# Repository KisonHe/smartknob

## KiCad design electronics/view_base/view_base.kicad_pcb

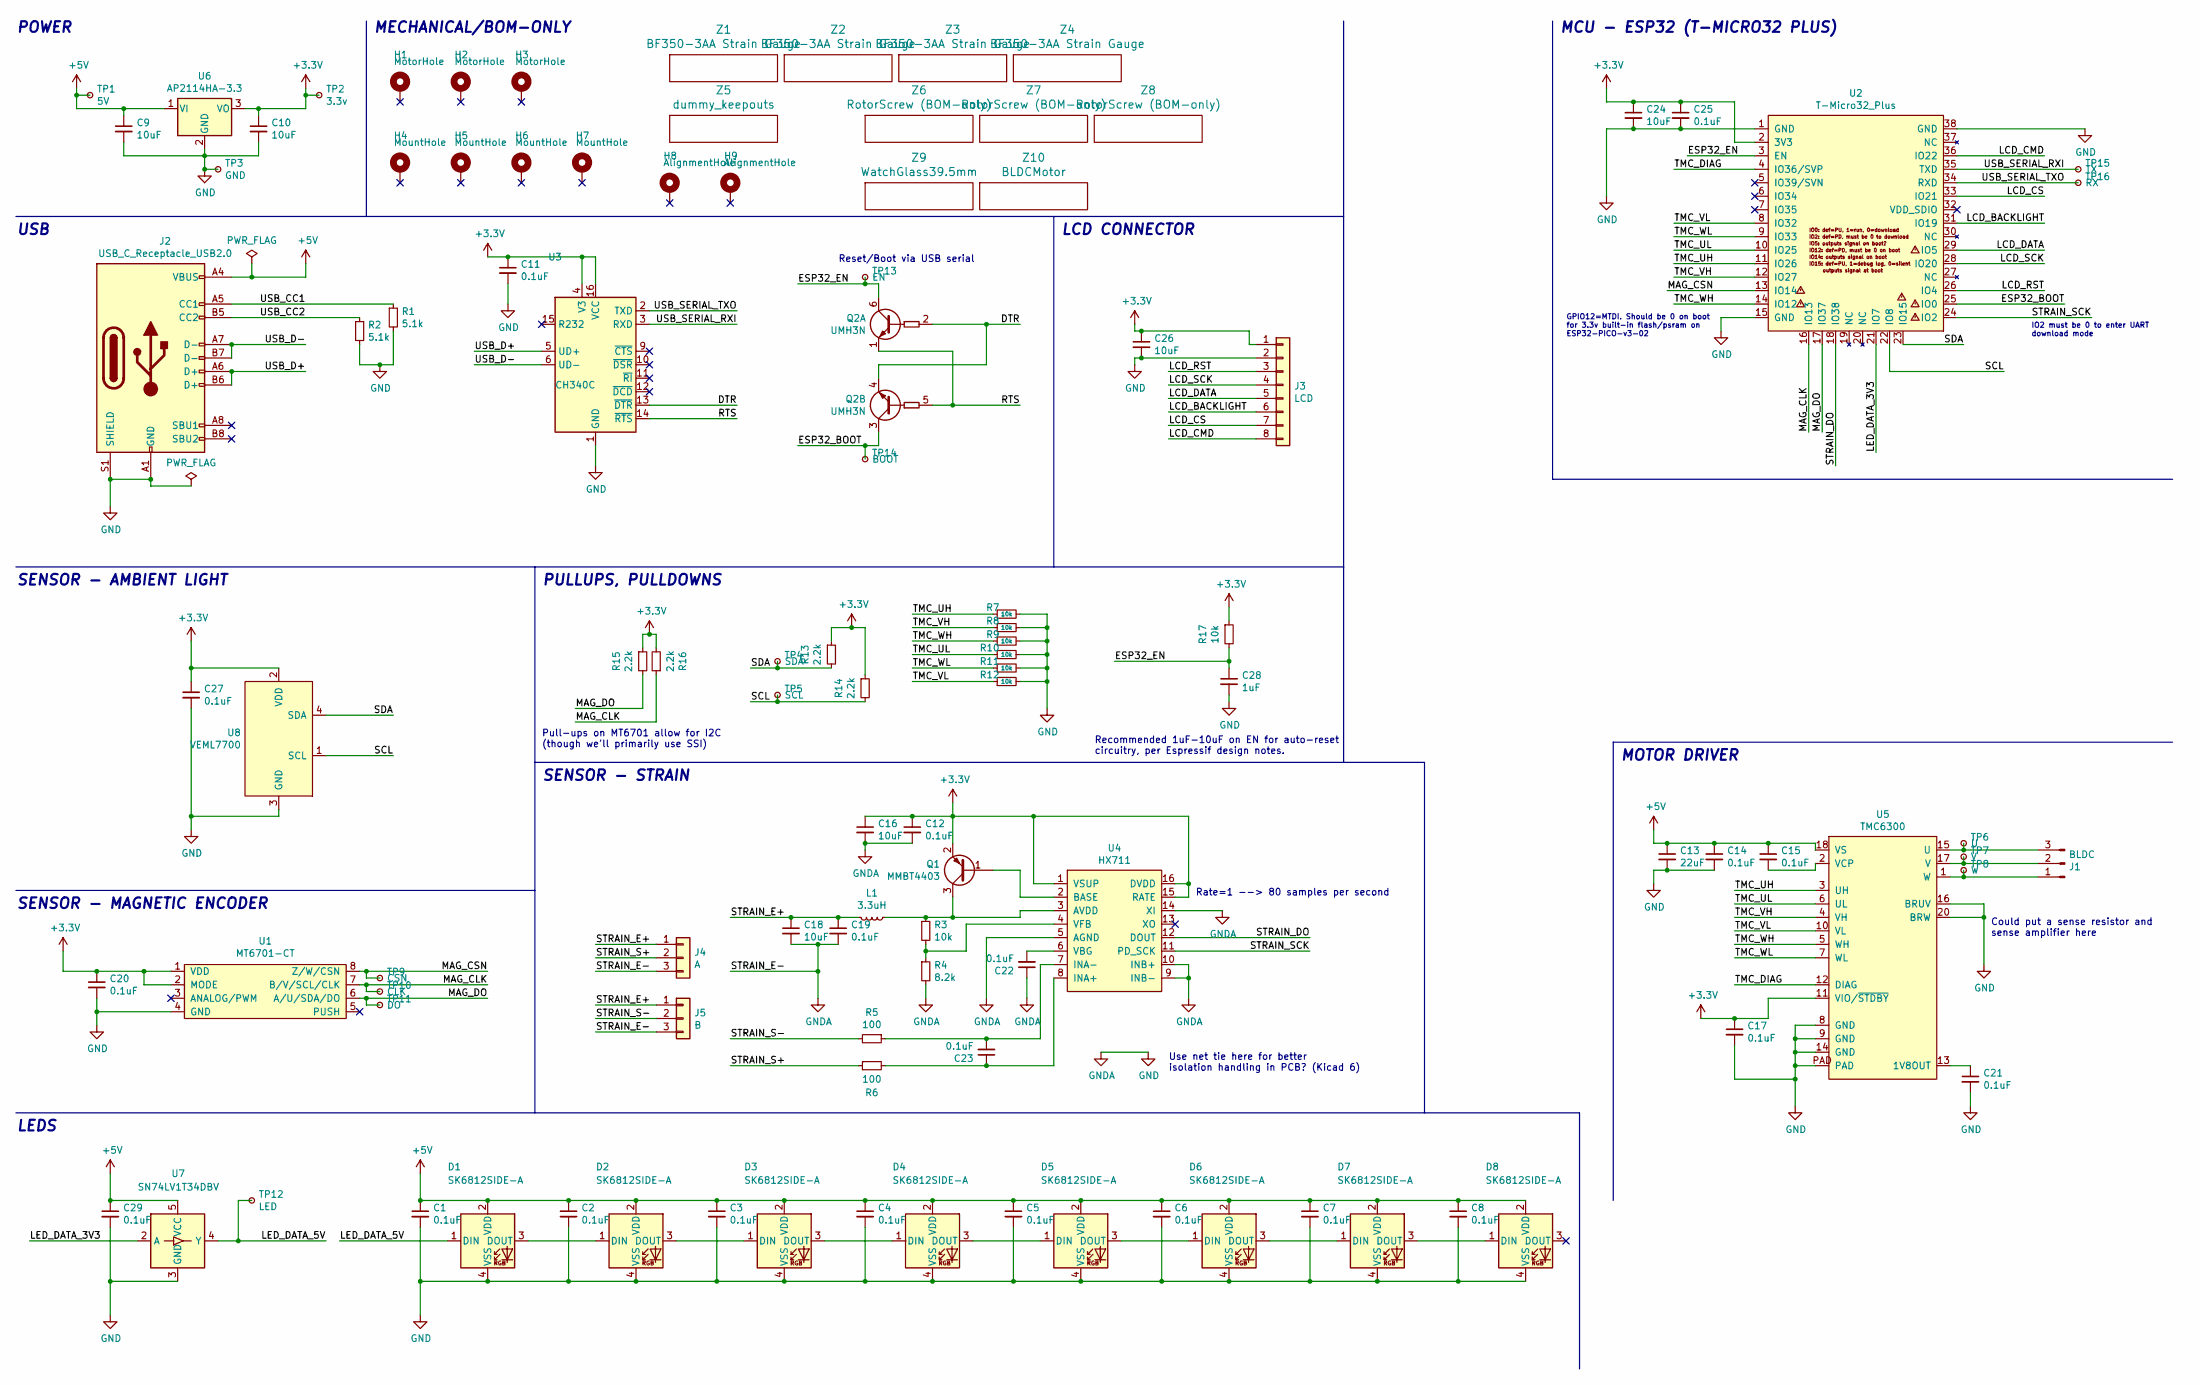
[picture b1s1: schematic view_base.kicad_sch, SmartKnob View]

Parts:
C1, C2, C3, C4, C5, C6, C7, C8, C11, C12, C14, C15, C17, C19, C20, C21, C22, C23, C25, C27, C29: 0.1uF; C_0603_1608Metric; LCSC C1591
C9, C10, C16, C18, C24, C26: 10uF; C_0805_2012Metric; LCSC C2922480
C13: 22uF; C_0805_2012Metric; LCSC C98190
C28: 1uF; C_0603_1608Metric; Mouser 187-CL10A105KA8NNNC
D1, D2, D3, D4, D5, D6, D7, D8: SK6812SIDE-A; SK6812-SIDE-A; Digikey 1528-4691-ND
H1, H2, H3: MotorHole; MountingHole_M1.6
H4, H5, H6, H7: MountHole; MountingHole_2.2mm_M2_ISO7380_Pad_NonVirtual
H8, H9: AlignmentHole; MountingHole_2.2mm_M2_ISO7380_Pad_NonVirtual
J1: BLDC; 532610371; LCSC C293630
J2: USB_C_Receptacle_USB2.0; USB4510_NoPaste; LCSC C428463
J3: LCD; SolderPads_2mm_8
J4: A; SolderPads_2mm_3_STRAIN
J5: B; SolderPads_2mm_3_STRAIN
L1: 3.3uH; L_0805_2012Metric; LCSC C307744
Q1: MMBT4403; SOT-23; LCSC C78864
Q2: UMH3N; SOT-363_SC-70-6; LCSC C62892
R1, R2: 5.1k; R_0603_1608Metric; LCSC C105580
R3, R7, R8, R9, R10, R11, R12, R17: 10k; R_0603_1608Metric; LCSC C98220
R4: 8.2k; R_0603_1608Metric; LCSC C114637
R5, R6: 100; R_0603_1608Metric; LCSC C319953
R13, R14, R15, R16: 2.2k; R_0603_1608Metric; LCSC C4190
TP1: 5V; TestPoint_Pad_D2.0mm_ValueSilk
TP2: 3.3v; TestPoint_Pad_D2.0mm_ValueSilk
TP3: GND; TestPoint_Pad_D2.0mm_ValueSilk
TP4: SDA; TestPoint_Pad_D2.0mm_ValueSilk
TP5: SCL; TestPoint_Pad_D2.0mm_ValueSilk
TP6: U; TestPoint_Pad_D2.0mm_ValueSilk
TP7: V; TestPoint_Pad_D2.0mm_ValueSilk
TP8: W; TestPoint_Pad_D2.0mm_ValueSilk
TP9: CSN; TestPoint_Pad_D2.0mm_ValueSilk
TP10: CLK; TestPoint_Pad_D2.0mm_ValueSilk
TP11: DO; TestPoint_Pad_D2.0mm_ValueSilk
TP12: LED; TestPoint_Pad_D2.0mm_ValueSilk
TP13: EN; TestPoint_Pad_D2.0mm_ValueSilk
TP14: BOOT; TestPoint_Pad_D2.0mm_ValueSilk
TP15: TX; TestPoint_Pad_D2.0mm_ValueSilk
TP16: RX; TestPoint_Pad_D2.0mm_ValueSilk
U1: MT6701-CT; SOIC-8_3.9x4.9mm_P1.27mm; LCSC C2856764
U2: T-Micro32_Plus; T-Micro32; Digikey N/A
U3: CH340C; SOIC-16_3.9x9.9mm_P1.27mm; LCSC C84681
U4: HX711; SOIC-16_3.9x9.9mm_P1.27mm; LCSC C43656
U5: TMC6300; QFN-20-1EP_3x3mm_P0.4mm_EP1.65x1.65mm_ThermalVias_LargerVia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; Digikey TMC6300-LA-T
U6: AP2114HA-3.3; SOT-223-3_TabPin2; LCSC C460314
U7: SN74LV1T34DBV; SOT-23-5; LCSC C100024
U8: VEML7700; VEML7700-TOP; Digikey VEML7700-TT
Z1, Z2, Z3, Z4: BF350-3AA Strain Gauge; BF350-3AA; Digikey N/A
Z5: dummy_keepouts; ViewKeepouts3d
Z6, Z7, Z8: RotorScrew (BOM-only); bom_only_no_pin
Z9: WatchGlass39.5mm; bom_only_no_pin
Z10: BLDCMotor; bom_only_no_pin

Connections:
+3V3: C10.1, C11.1, C12.1, C16.1, C17.1, C20.1, C24.1, C25.1, C26.1, C27.1, J3.1, Q1.2 (E), R13.1, R14.1, R15.1, R16.2, R17.1, TP2.1, U1.1 (VDD), U1.2 (MODE), U2.2 (3V3), U3.4 (V3), U3.16 (VCC), U4.1 (VSUP), U4.15 (RATE), U4.16 (DVDD), U5.11 (VIO/~STDBY), U6.3 (VO), U8.2 (VDD)
+5V: C1.1, C2.1, C3.1, C4.1, C5.1, C6.1, C7.1, C8.1, C9.1, C13.1, C14.1, C15.1, C29.1, D1.2 (VDD), D2.2 (VDD), D3.2 (VDD), D4.2 (VDD), D5.2 (VDD), D6.2 (VDD), D7.2 (VDD), D8.2 (VDD), J2.A4 (VBUS), J2.A9 (VBUS), J2.B4 (VBUS), J2.B9 (VBUS), TP1.1, U5.18 (VS), U6.1 (VI), U7.5 (VCC)
/DTR: Q2.2 (B1), Q2.4 (E2), U3.13 (~DTR)
/ESP32_BOOT: Q2.3 (C2), TP14.1, U2.25 (IO0)
/ESP32_EN: C28.1, Q2.6 (C1), R17.2, TP13.1, U2.3 (EN)
/LCD_BACKLIGHT: J3.6, U2.31 (IO19)
/LCD_CMD: J3.8, U2.36 (IO22)
/LCD_CS: J3.7, U2.33 (IO21)
/LCD_DATA: J3.5, U2.29 (IO5)
/LCD_RST: J3.3, U2.26 (IO4)
/LCD_SCK: J3.4, U2.28 (IO20)
/LED_DATA_3V3: U2.21 (IO7), U7.2 (A)
/LED_DATA_5V: D1.1 (DIN), TP12.1, U7.4 (Y)
/MAG_CLK: R16.1, TP10.1, U1.7 (B/V/SCL/CLK), U2.16 (IO13)
/MAG_CSN: TP9.1, U1.8 (Z/W/CSN), U2.13 (IO14)
/MAG_DO: R15.2, TP11.1, U1.6 (A/U/SDA/DO), U2.17 (IO37)
/RTS: Q2.1 (E1), Q2.5 (B2), U3.14 (~RTS)
/SCL: R14.2, TP5.1, U2.22 (IO8), U8.1 (SCL)
/SDA: R13.2, TP4.1, U2.23 (IO15), U8.4 (SDA)
/STRAIN_DO: U2.18 (IO38), U4.12 (DOUT)
/STRAIN_E+: C18.1, C19.1, J4.1, J5.1, L1.2
/STRAIN_S+: J4.2, R6.1
/STRAIN_S-: J5.2, R5.2
/STRAIN_SCK: U2.24 (IO2), U4.11 (PD_SCK)
/TMC_DIAG: U2.4 (IO36/SVP), U5.12 (DIAG)
/TMC_UH: R7.1, U2.11 (IO26), U5.3 (UH)
/TMC_UL: R10.1, U2.10 (IO25), U5.6 (UL)
/TMC_VH: R8.1, U2.12 (IO27), U5.4 (VH)
/TMC_VL: R12.1, U2.8 (IO32), U5.10 (VL)
/TMC_WH: R9.1, U2.14 (IO12), U5.5 (WH)
/TMC_WL: R11.1, U2.9 (IO33), U5.7 (WL)
/USB_CC1: J2.A5 (CC1), R1.1
/USB_CC2: J2.B5 (CC2), R2.1
/USB_D+: J2.A6 (D+), J2.B6 (D+), U3.5 (UD+)
/USB_D-: J2.A7 (D-), J2.B7 (D-), U3.6 (UD-)
/USB_SERIAL_RXI: TP15.1, U2.35 (TXD), U3.3 (RXD)
/USB_SERIAL_TXO: TP16.1, U2.34 (RXD), U3.2 (TXD)
GND: C1.2, C2.2, C3.2, C4.2, C5.2, C6.2, C7.2, C8.2, C9.2, C10.2, C11.2, C12.2, C13.2, C14.2, C16.2, C17.2, C18.2, C19.2, C20.2, C21.2, C22.1, C24.2, C25.2, C26.2, C27.2, C28.2, C29.2, D1.4 (VSS), D2.4 (VSS), D3.4 (VSS), D4.4 (VSS), D5.4 (VSS), D6.4 (VSS), D7.4 (VSS), D8.4 (VSS), J2.A1 (GND), J2.A12 (GND), J2.B1 (GND), J2.B12 (GND), J2.S1 (SHIELD), J3.2, J4.3, J5.3, R1.2, R2.2, R4.2, R7.2, R8.2, R9.2, R10.2, R11.2, R12.2, TP3.1, U1.4 (GND), U2.1 (GND), U2.15 (GND), U2.38 (GND), U3.1 (GND), U4.5 (AGND), U4.9 (INB-), U4.10 (INB+), U4.14 (XI), U5.8 (GND), U5.9 (GND), U5.14 (GND), U5.16 (BRUV), U5.20 (BRW), U5.PAD, U6.2 (GND), U7.3 (GND), U8.3 (GND)
unnamed: C15.2, U5.2 (VCP)
unnamed: C21.1, U5.13 (1V8OUT)
unnamed: C22.2, U4.6 (VBG)
unnamed: C23.1, R6.2, U4.8 (INA+)
unnamed: C23.2, R5.1, U4.7 (INA-)
unnamed: D1.3 (DOUT), D2.1 (DIN)
unnamed: D2.3 (DOUT), D3.1 (DIN)
unnamed: D3.3 (DOUT), D4.1 (DIN)
unnamed: D4.3 (DOUT), D5.1 (DIN)
unnamed: D5.3 (DOUT), D6.1 (DIN)
unnamed: D6.3 (DOUT), D7.1 (DIN)
unnamed: D7.3 (DOUT), D8.1 (DIN)
unnamed: J1.1, TP8.1, U5.1 (W)
unnamed: J1.2, TP7.1, U5.17 (V)
unnamed: J1.3, TP6.1, U5.15 (U)
unnamed: L1.1, Q1.3 (C), R3.1, U4.3 (AVDD)
unnamed: Q1.1 (B), U4.2 (BASE)
unnamed: R3.2, R4.1, U4.4 (VFB)

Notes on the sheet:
Pull-ups on MT6701 allow for I2C (though we'll primarily use SSI)
Rate=1 --> 80 samples per second
Reset/Boot via USB serial
PULLUPS, PULLDOWNS
SENSOR - AMBIENT LIGHT
MCU - ESP32 (T-MICRO32 PLUS)
MOTOR DRIVER
SENSOR - STRAIN
LEDS
POWER
SENSOR - MAGNETIC ENCODER
USB
IO2 must be 0 to enter UART download mode
Recommended 1uF-10uF on EN for auto-reset circuitry, per Espressif design notes.
MECHANICAL/BOM-ONLY
GPIO12=MTDI. Should be 0 on boot for 3.3v built-in flash/psram on ESP32-PICO-v3-02
LCD CONNECTOR
Use net tie here for better isolation handling in PCB? (Kicad 6)
Could put a sense resistor and sense amplifier here

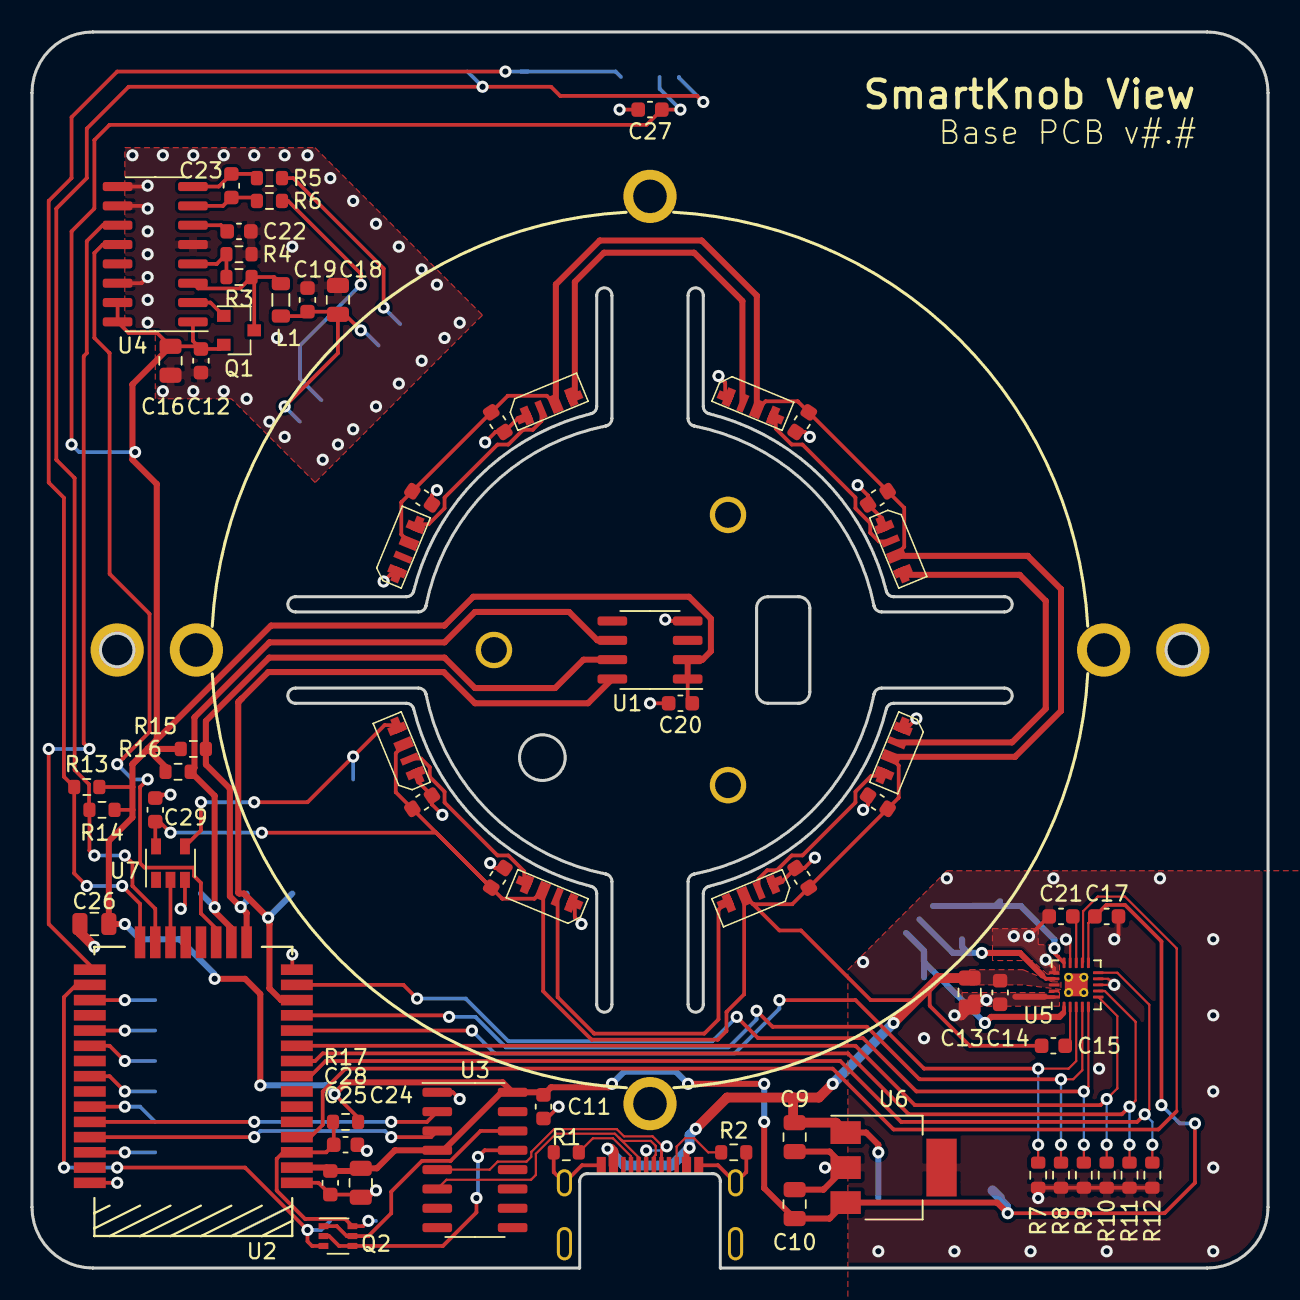
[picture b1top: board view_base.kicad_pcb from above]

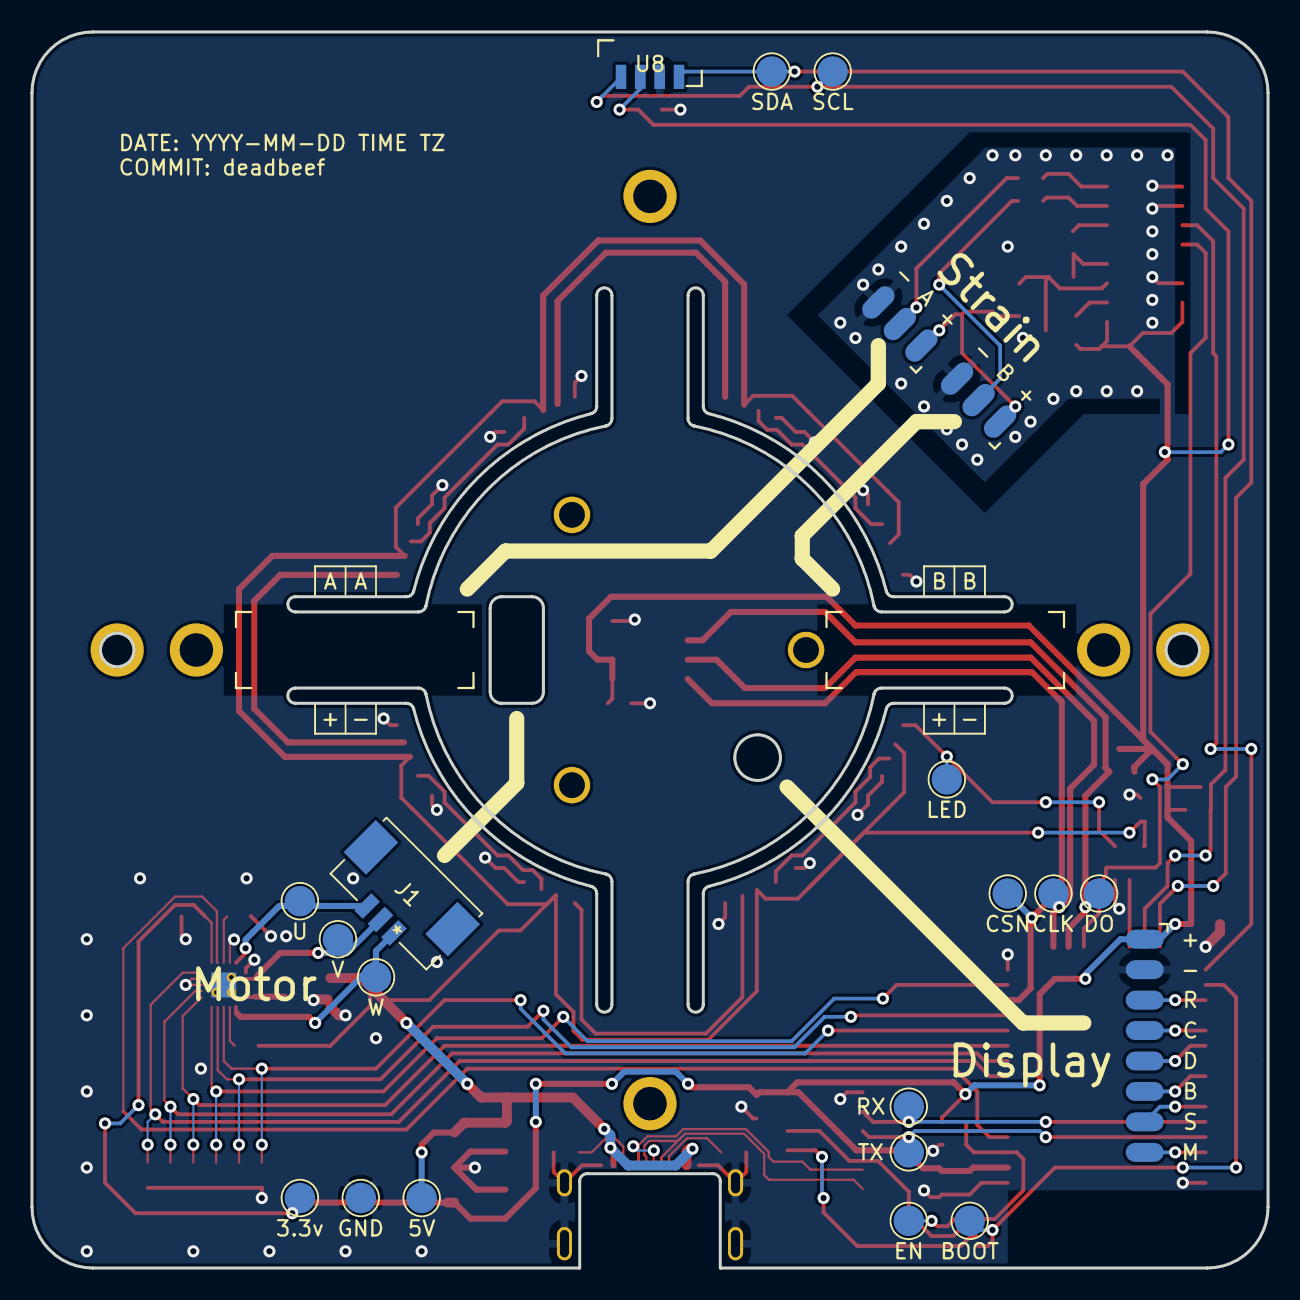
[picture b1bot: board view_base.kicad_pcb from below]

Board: 2 copper layers, 81.2 x 81.2 mm, 105 parts (25 on the bottom side), 56 nets.

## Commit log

2022-06-19 Add comments
2022-06-19 Add more comments
2022-06-19 Read somemore comments
2022-07-05 New motor suffers

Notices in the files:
parts and their libraries:
Copyright 2021 Accelerated Designs. All rights reserved.
